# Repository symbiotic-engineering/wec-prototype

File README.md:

# Wave Energy Converter (WEC) Prototype Control System

## 1. Project Overview
Control system for testing **wave energy converter (WEC) prototypes** using a **Raspberry Pi touchscreen UI** and **Arduino motor control**.  
The system allows real-time interaction with prototypes, including selecting WEC type, adjusting frequency/amplitude, and running tests.

## 2. Components / Hardware
- **Raspberry Pi** – Runs the touchscreen UI  
- **Arduino Mega** – Controls the motor  
- **VESC & VESC Express** – Motor controller and Data Logger  
- **WEC prototypes** – Point Absorber and Oscillating Flap types  
- **Touchscreen** – User interface for control  

## 3. Software
- **Python** – Raspberry Pi GUI and control code (`wec_rpi_gui.py`)  
- **MATLAB** – Hydrodynamic analyses (`PA_buoyancy.m`) 
- **Arduino** – Motor control code (`wec_arduino_motorcontrol.ino`)  
- **VESC logging script** (`log_can.lisp`) – Captures motor data points  

## 4. Folder Structure 
```
WEC-Prototype/
├── Arduino_Mega/
│ └── wec_arduino_motorcontrol.ino # Arduino firmware controlling motor based on RPi commands
├── CAD/
│ └── Multiple CAD pdf files
├── Raspberry_Pi/
│ └── wec_rpi_gui.py # Python UI for controlling WEC tests
└── VESC/
└── log_can.lisp # Logs motor data points during testing
├── hydrodynamics/
  └── PA_buoyancy.m # Evaluates the hydrodynamic repsonse of the PA
├── gear_ratio_appendix/
  └── Files required to simulate both the PA and OSWEC to estimate required GR
```
## 5. Code Setup Instructions

1. **Raspberry Pi**  
   - Copy `wec_rpi_gui.py` to the Pi.  
   - Configure the script to run automatically using **cron**.  
   - Connect Raspberry Pi to Arduino via USB.  

2. **Arduino Mega**  
   - Flash `wec_arduino_motorcontrol.ino` onto the Arduino.  
   - Ensure the **VESC UART library** is downloaded from GitHub and stored in Arduino’s libraries folder.  

3. **VESC / VESC Express**  
   - Flash firmware and edit log_can.lisp to VESC and VESC Express.  

4. **Dependencies & Hardware Connections**  
   - Proper USB connection between Pi and Arduino.  
   - Ensure VESC and motor connections are secure before powering the system.  

## 6. Usage Instructions

1. Power on Raspberry Pi and Arduino.  
2. Start the Python UI (`wec_rpi_gui.py`) via touchscreen or cron.  
3. Select the WEC type (Point Absorber or Oscillating Flap).  
4. Verify that all **electrical connections** are secure.  
5. Run tests by selecting frequency/amplitude options in the UI.  
6. Data from the VESC can be logged using `log_can.lisp`.

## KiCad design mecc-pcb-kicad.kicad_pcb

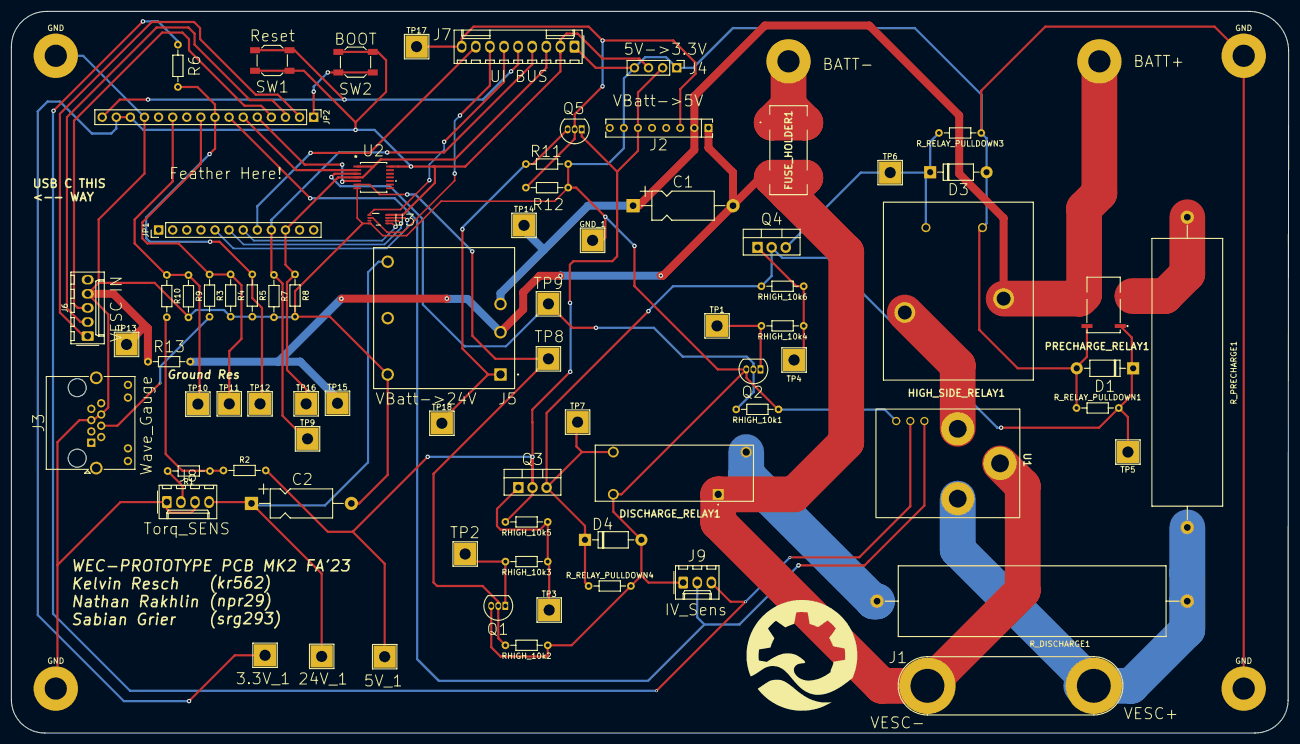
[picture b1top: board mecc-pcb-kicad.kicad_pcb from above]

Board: 2 copper layers, 230.1 x 130.0 mm, 81 parts (0 on the bottom side), 44 nets.

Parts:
3.3V_1, 5V_1, 24V_1: TestPoint; TestPoint_THTPad_4.0x4.0mm_Drill2.0mm
C1: 100 uF; CP_Axial_L11.0mm_D5.0mm_P18.00mm_Horizontal
C2: 47 uF; CP_Axial_L11.0mm_D5.0mm_P18.00mm_Horizontal
D1, D3, D4: 1N4007; D_DO-41_SOD81_P10.16mm_Horizontal
DISCHARGE_RELAY1: 2-1393224-6; 213932246
FUSE_HOLDER1: 01000065Z
GND: MountingHole_4mm_Pad
GND#2, GND#3, GND#4: MountingHole_4mm_Pad
GND_1: TestPoint; TestPoint_THTPad_4.0x4.0mm_Drill2.0mm
HIGH_SIDE_RELAY1: J115F11AH12VDCSH1.5U; J115F11AH12VDCSH15U
J1: VESC Term; Banana_Jack_2Pin
J2: VBatt -> 5V; SIP-8_19x3mm_P2.54mm
J3: Wave_Gauge; RJ45_Amphenol_RJHSE538X
J4: 5V -> 3.3V; PinHeader_1x04_P2.54mm_Vertical
J5: PDQE15-Q48-D24-D; CONV_PDQE15-Q48-D24-D
J6: VESC IN; Molex_KK-254_AE-6410-05A_1x05_P2.54mm_Vertical
J7: UI BUS; Molex_KK-254_AE-6410-09A_1x09_P2.54mm_Vertical
J8: Torq_SENS; Molex_KK-254_AE-6410-04A_1x04_P2.54mm_Vertical
J9: IV_Sens; Molex_KK-254_AE-6410-03A_1x03_P2.54mm_Vertical
JP1: HEADER-1X12; PinHeader_1x12_P2.54mm_Vertical
JP2: HEADER-1X16ROUND; PinHeader_1x16_P2.54mm_Vertical
PRECHARGE_RELAY1: IMB03CGR
Q1, Q2, Q5: NMOS; WEC_NMOS
Q3, Q4: PMOS; WEC_PMOS
R1, R2: 3k; R_Axial_DIN0204_L3.6mm_D1.6mm_P7.62mm_Horizontal
R3, R5, R7, R8, R11, R12: 10k; R_Axial_DIN0204_L3.6mm_D1.6mm_P7.62mm_Horizontal
R4: 5k; R_Axial_DIN0204_L3.6mm_D1.6mm_P7.62mm_Horizontal
R6: 27k; R_Axial_DIN0204_L3.6mm_D1.6mm_P7.62mm_Horizontal
R9: 100k; R_Axial_DIN0204_L3.6mm_D1.6mm_P7.62mm_Horizontal
R10: 50k; R_Axial_DIN0204_L3.6mm_D1.6mm_P7.62mm_Horizontal
R13: 0; R_Axial_DIN0204_L3.6mm_D1.6mm_P7.62mm_Horizontal
RHIGH_10k1, RHIGH_10k2, RHIGH_10k3, RHIGH_10k4, RHIGH_10k5, RHIGH_10k6: 10k; R_Axial_DIN0204_L3.6mm_D1.6mm_P7.62mm_Horizontal
R_DISCHARGE1: R; R_Axial_Power_L48.0mm_W12.5mm_P55.88mm
R_PRECHARGE1: R; R_Axial_Power_L48.0mm_W12.5mm_P55.88mm
R_RELAY_PULLDOWN1, R_RELAY_PULLDOWN3, R_RELAY_PULLDOWN4: 40k; R_Axial_DIN0204_L3.6mm_D1.6mm_P7.62mm_Horizontal
SW1, SW2: Reset; SW_SPST_SKQG_WithoutStem
TP1, TP2, TP3, TP4, TP5, TP6, TP7, TP8, TP9, TP9#2, TP10, TP11, TP12, TP13, TP14, TP15, TP16, TP17, TP18: TestPoint; TestPoint_THTPad_4.0x4.0mm_Drill2.0mm
U1: SEN-16407
U2: SN74HCS09QPWRQ1; SO14_PW_TEX
U3: SN74LVC1G139DCUR; DCU0008A_N

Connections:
+3.3V: 3.3V_1.1, J4.3, J7.2, JP2.14, JP2.15, SW1.1, SW2.1, U2.14 (VCC), U3.8 (VCC)
+5V: 5V_1.1, J2.6, J4.2, Q3.1 (D), Q5.3 (D), R2.2, RHIGH_10k5.2
+24V: 24V_1.1, C2.1, J5.4 (+VO), J8.4
/A1: JP2.11, R9.1, R10.2, TP10.1
/A3: JP2.9, R3.1, R4.2, TP11.1
/A4: JP2.8, R5.2, R6.2, TP12.1
ADVANCE_BUTTON_RED: J7.4, JP1.9, R7.2, TP9.1
BATT_CURR_SENSOR: J9.2, JP2.7, U1.6 (Iout)
BATT_NEG: FUSE_HOLDER1.1, FUSE_HOLDER1.4
BATT_POS: C1.1, HIGH_SIDE_RELAY1.2 (COM), J2.2, J5.3 (VIN), PRECHARGE_RELAY1.6 (NO), TP14.1
BATT_V_SENSOR: J9.3, R6.1, U1.7 (Vout)
BOOT0: JP2.1, SW2.2
DCDC_SW: J2.3, J7.9, Q5.2 (G), R12.1, TP17.1
GND: C2.2, D1.2 (A), D3.2 (A), D4.2 (A), DISCHARGE_RELAY1.A1 (COIL_1), GND.1, GND#2.1, GND#3.1, GND#4.1, GND_1.1, HIGH_SIDE_RELAY1.4 (COIL_2), J2.7, J3.5, J3.6, J4.1, J4.4, J5.6 (-VO), J6.4, J7.1, J8.1, J8.3, J9.1, JP2.13, PRECHARGE_RELAY1.8 (SET-/RESET+), Q1.1 (S), Q2.1 (S), R4.1, R5.1, R7.1, R8.1, R9.2, R11.2, R12.2, R13.1, RHIGH_10k1.1, RHIGH_10k2.1, R_RELAY_PULLDOWN1.1, R_RELAY_PULLDOWN3.1, R_RELAY_PULLDOWN4.2, TP13.1, U1.8 (SIG_GND), U2.7 (GND), U3.4 (GND)
HIGH_IN: JP2.6, U2.2 (1B)
HIGH_SIDE: D3.1 (K), HIGH_SIDE_RELAY1.3 (COIL_1), Q4.3 (S), R_RELAY_PULLDOWN3.2, TP6.1
HIGH_SIDE_ANDOUT: Q2.2 (G), RHIGH_10k1.2, TP9#2.1, U2.3 (1Y)
IO_ESTOP: J7.3, JP1.10, R8.2, TP16.1, U2.1 (1A), U2.4 (2A)
LOW_IN: JP2.5, U2.5 (2B)
unnamed: DISCHARGE_RELAY1.12 (NC), R_DISCHARGE1.1
unnamed: HIGH_SIDE_RELAY1.1 (NO), U1.4 (+IN)
unnamed: J5.1 (CTRL), Q5.1 (S), R11.1, TP18.1
unnamed: PRECHARGE_RELAY1.3 (COM), R_PRECHARGE1.2
unnamed: Q1.3 (D), RHIGH_10k3.2, TP2.1
unnamed: Q2.3 (D), RHIGH_10k4.2, TP1.1
unnamed: Q3.2 (G), RHIGH_10k3.1, RHIGH_10k5.1, TP3.1
unnamed: Q4.2 (G), RHIGH_10k4.1, RHIGH_10k6.1, TP4.1
unnamed: R1.2, R2.1, R10.1
PRE_DIS: D1.1 (K), D4.1 (K), DISCHARGE_RELAY1.A2 (COIL_2), PRECHARGE_RELAY1.1 (SET+/RESET-), Q3.3 (S), Q4.1 (D), RHIGH_10k6.2, R_RELAY_PULLDOWN1.2, R_RELAY_PULLDOWN4.1, TP5.1, TP7.1
PRE_DIS_ANDOUT: Q1.2 (G), RHIGH_10k2.2, TP8.1, U2.6 (2Y)
RESET: J7.5, JP2.16, SW1.2
Ref_Model_SW: J7.8, JP1.8
TORQUE_SENSOR: J8.2, R1.1
TORQ_SWITCH_1: J7.6, U3.1 (A)
TORQ_SWITCH_2: J7.7, U3.2 (B)
Torq_SW_Mode_1: JP1.5, U3.7 (Y0)
Torq_SW_Mode_2: JP1.6, U3.6 (Y1)
Torq_SW_Mode_3: JP1.7, U3.5 (Y2)
VESC_INPUT: J6.2, JP2.3
VESC_NEG: C1.2, DISCHARGE_RELAY1.11 (COM), FUSE_HOLDER1.2, FUSE_HOLDER1.3, J1.2, J2.1, J5.2 (GND), R13.2, TP15.1, U1.2 (GND)
VESC_OUTPUT: J6.1, JP2.2
VESC_POS: J1.1, R_DISCHARGE1.2, R_PRECHARGE1.1, U1.5 (+OUT)
VESC_POWER_SWITCH: J6.3, JP2.4
WAVE_GAUGE: J3.4, R3.2

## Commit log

2022-11-25 Skeleton for the FSM
2022-11-25 Declared some variables
2022-12-02 Values & returns
2022-12-02 more info on outputs and parameters
2022-12-02 Began void loop
2022-12-02 Implemented uart vesc readings
2022-12-03 add uart file
2022-12-03 Add files via upload
    Needs to be merged with fsm code.
2022-12-10 VescUART & Hardware Serial Libraries
2022-12-10 filled in library materials
2022-12-10 start fixing logic errors in fault detect code
2022-12-10 Deleted .git directories
2022-12-10 uart progress
2022-12-10 uart files are updated, error is to recognize serial
2022-12-13 Needs a bit for integration
    Currently just .txt. Time is set as time since Arduino started running, a different time is possible, but I don't see a reason why this wouldn't work. Probably needs more sensor outs, but should be p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
2022-12-13 Added link to library
2023-02-19 push everything from lab computer from end of last semester
2023-03-16 SolidGeek Library Implementation
2023-03-20 sensor updates
2023-03-21 Added working FSM checkpoint
2023-03-22 wave tank script
2023-04-10 sensor code updates
2023-04-13 bugfixing in progress
2023-04-14 sensor updates: torque sensor resistor network
2023-05-11 Rename RM5wood.m to RM5stiffness_inertia_calcs.m
2023-05-18 sensors
2023-09-08 Create LICENSE
2023-10-10 Upload Nelsons PCB files from last semester
2023-10-10 Create sensor-board-connection-list
    This file lists what the sensor board connects to
2023-10-10 Update sensor-board-connection-list
2023-10-23 initial working sim with dummy numbers
2023-10-29 merged with Nathan's branch
2023-10-29 Implemented all of list except for CMOS stuff
2023-11-02 Implemented some of becca's changes
2023-11-02 Fixing Becca's Comments 11-2-23
2023-11-02 I don't even think I made changes I'm just paranoid
2023-11-02 Becca's messages
2023-11-02 Added a PGND and AGND connection, and cleaned up some routing.
2023-11-07 Implemented Becca's comments. Board should be ready for final review
2023-11-09 Added Gerber files
2023-11-10 being paranoid and pushing to make sure
2023-11-14 changed pulldown resistor values to match the resistors we have in the lab (5.1k)
2023-12-14 commiting whatever is on my laptop. I think it's the same as what's already in the branch.
2023-12-14 commiting for merge to main
2024-02-22 edited frictionsim not functional
2024-05-14 olivias changes to run oswec real hydro data and sweep spring and GR
2024-05-14 restructure loop and add graph to show valid combinations
2024-05-16 added functions to folder
2024-05-16 actually adding the files needed to run wamit
2024-06-11 add control value changes from 5/25/23 wave tank testing
2024-06-11 move to folder so arduino ide can open files
2024-06-11 add sd card code (mostly commented) from sabian zip file
2024-06-11 add better comments and update for oregon numbers
2024-06-11 move friction sim stuff to hydro folder
2024-07-02 add missing wecsim dependencies
2024-07-02 comment out the bits I think are wrong / dont make sense
2024-07-02 rename Hs to H to reflect regular wave not irregular
2024-07-03 clean up hydro coeffs, add motor torque output, and make work for rm3 too
2024-07-03 add matlab asv to gitignore
2024-07-03 readability tweak on tank depths
2024-07-10 still exist errors and k value doesn't make sense
2024-07-17 7/17/24 - fixed k calculation and began adjusting factors for using marine foam
2024-08-14 update with real values of flap inertia and frequency, and add forced oscillation radiation test sim
2024-09-10 add wave height sweep and ability to sim RM5 without string-spring
2024-09-10 rename file to reflect GR choice as actual purpose
2024-09-10 rename to reflect static friction emphasis
2024-09-10 fix plotting, still a lot of zero results
2024-09-10 fix lines on graph for single spring size
2024-09-10 turn plots into subplots, turn off friction, show NaN as white
2024-09-10 lower the torque for radiation test to get it unstuck
2024-09-10 results for tonight: RM3 vs 5 labelled, full size figures
2024-09-17 change moment of inertia to include curved rack
2024-09-19 fixed frequencies, added rm3.out file to folder
2024-09-19 STM Test Code from Summer 2024
    This was the code used to test if the STM was connected properly and if we could consistently send messages between STM & laptop over Serial.
2024-10-01 changes to state machine code to send microcontroller back to boot once powered down
2024-10-01 updated to print actual battery voltage
2024-11-08 added everything to correct paths and altered code to be accurate to hardware
2024-11-26 Updated SD card test code
2025-01-08 Create WEC_sys2.ino
    Code modifications done over winter break. Still needs to be tested and tweaked
2025-01-21 Rename UnoTest.ino to MegaTest.ino
2025-01-21 Rename UnoTest (1).ino to megaTestv2.ino
2025-01-21 Rename start_stop_v3.py to Rpi_UI_v2.py
2025-01-21 Rename Rpi_UI_v2.py to rpi_UI_v2.py
2025-01-24 added and updated the calcVoltage.ino file to include calculations for the controller damping and stiffness
2025-03-11 Create log_can.lisp
    This is the lisp script uploaded to both the VESC and VESC Express through Vesc Tool to log the right fields of data
2025-03-12 edited the vescexpress logging commands
2025-03-14 corrected "thetha" mistake, fixed effective radius of PA pinion
2025-03-14 fixed pinion PA radius, fixed "thetha" error
2025-03-17 creates a sinusoidal current input to mimic waves
2025-08-26 updating all the files that we hadn't pushed in a while.....
2025-08-26 adding CAD to the most up to date branch
2025-08-27 Create wec_rpi_gui.py
    This is the code that runs on the Rpi to display the Graphical User Interface (GUI) on the touchscreen. It allows testers to select test parameters like frequency, amplitude and WEC type.
2025-08-27 Update wec_arduino_motorcontrol.ino
    Final motor controls code that runs on the Arduino Mega.
2025-08-27 Create log_can.lisp
    .lisp that controls the data points logged by the VESC. Note that this script must be the exact same in both the VESC and VESC Express to perform proper logging
2025-08-28 added PA_buoyancy script to jmd branch
2025-08-28 added gear ratio scripts to jmd branch
2025-08-28 updated README to reflect purpose of branch
2025-08-28 edited README to include new files, moved around a few files to their proper locations
2025-09-04 fixed these calculations and plots
